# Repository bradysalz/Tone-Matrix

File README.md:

# Tone-Matrix
Analog Tone Matrix. Inspired by [this](http://tonematrix.audiotool.com/). High level block diagram:

Follow along [here](https://bradysalz.com/tags/tone-matrix/) for more info!

## Project Structure

- `sim/`: LTSpice simulation testbenches/schematics 
- `plot/`: Sim data + Python plotting code 
- `kicad/`: KiCad schematics + PCB layout

Most of the `plot/` folder is just data dumps. I use Spyder as my MATLAB-esque IDE, which means I get to be lazy and use cells instead of neatly defining functions or files. Would not recommend running by itself - too many plots!

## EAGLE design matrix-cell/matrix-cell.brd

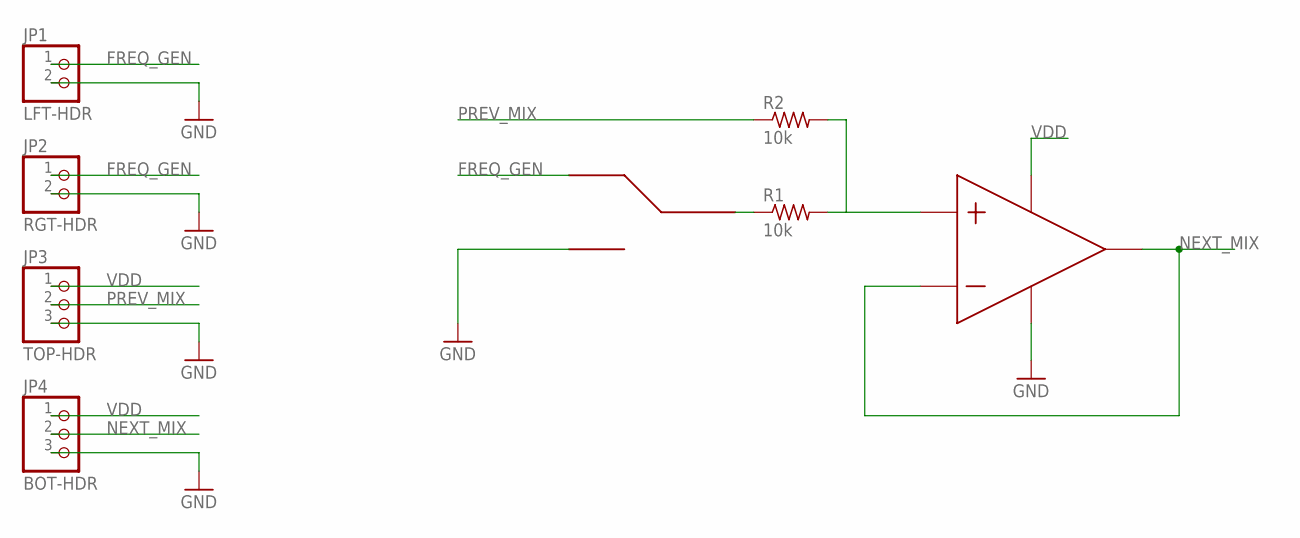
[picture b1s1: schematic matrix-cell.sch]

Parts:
JP1: LFT-HDR; 1X02/90
JP2: RGT-HDR; 1X02/90
JP3: TOP-HDR; 1X03/90
JP4: BOT-HDR; 1X03/90
R1, R2: 10k; R1206
U$1: RA1-SWITCH; RA11131100-SWITCH
U$2: MCP4162-OPAMP; SO08

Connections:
FREQ_GEN: JP1.1, JP2.1, U$1.R (NO)
GND: JP1.2, JP2.2, JP3.3, JP4.3, U$1.L (NC), U$2.4 (VSS)
unnamed: R1.2, R2.2, U$2.3 (NON-INV)
unnamed: R1.1, U$1.C (COMM)
NEXT_MIX: JP4.2, U$2.2 (INV), U$2.6 (OUT)
PREV_MIX: JP3.2, R2.1
VDD: JP3.1, JP4.1, U$2.7 (VDD)

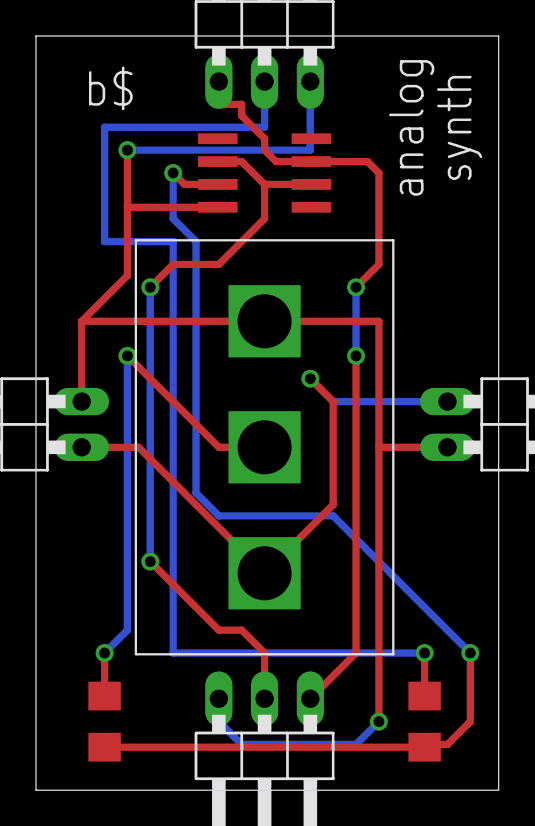
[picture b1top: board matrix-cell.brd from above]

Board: 2 copper layers, 25.7 x 41.9 mm, 8 parts (0 on the bottom side), 7 nets.

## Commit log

2015-08-12 Update LICENSE
2015-08-14 kicad why
    i surrender
2015-08-24 added signal generator
2015-08-24 added pins to signal generator
2015-11-15 library init
2015-11-15 matrix init
2015-11-15 finished cell
2017-04-25 fresh start boys
2017-04-25 updated gitignore
2017-04-25 initial schmitt trigger sims
2017-04-25 integrator and schmitt+integrator
2017-04-26 integrator cleanup
2017-04-26 sallen key filter schem
2017-04-26 sallen key plots
2017-04-27 square/tri/sine gen done
2017-04-28 Kicad init, working on oscillator
2017-04-28 updated full osc netlist
2017-04-28 stupid eaglecad gitignore messing with me
2017-04-28 undoing gitignore problems
2017-06-12 updating gitignore for FFT files
2017-06-12 adding voltage summer simulations
2017-07-13 updating gitignore
2017-07-13 [kicad] init the oscillator schematics
    Have the basic oscillator chain schem'd so far. Still need to add
    connectors, control bits, and switches for the output.
2017-08-06 updating fullosc schem
2017-08-06 [kicad] osc schem done
